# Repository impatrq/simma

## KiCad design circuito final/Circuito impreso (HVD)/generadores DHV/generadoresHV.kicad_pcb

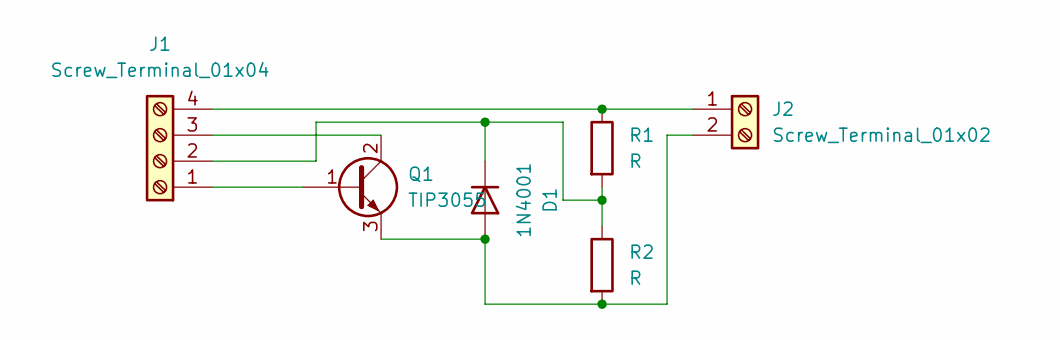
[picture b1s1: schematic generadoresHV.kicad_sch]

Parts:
D1: 1N4001; D_DO-41_SOD81_P10.16mm_Horizontal
J1: Screw_Terminal_01x04; TerminalBlock_bornier-4_P5.08mm
J2: Screw_Terminal_01x02; TerminalBlock_bornier-2_P5.08mm
Q1: TIP3055; TO-218-3_Vertical
R1, R2: R; R_Axial_Power_L20.0mm_W6.4mm_P7.62mm_Vertical

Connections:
unnamed: D1.1 (K), J1.2, R1.2, R2.1
unnamed: D1.2 (A), J2.2, Q1.3 (E), R2.2
unnamed: J1.1, Q1.1 (B)
unnamed: J1.3, Q1.2 (C)
unnamed: J1.4, J2.1, R1.1

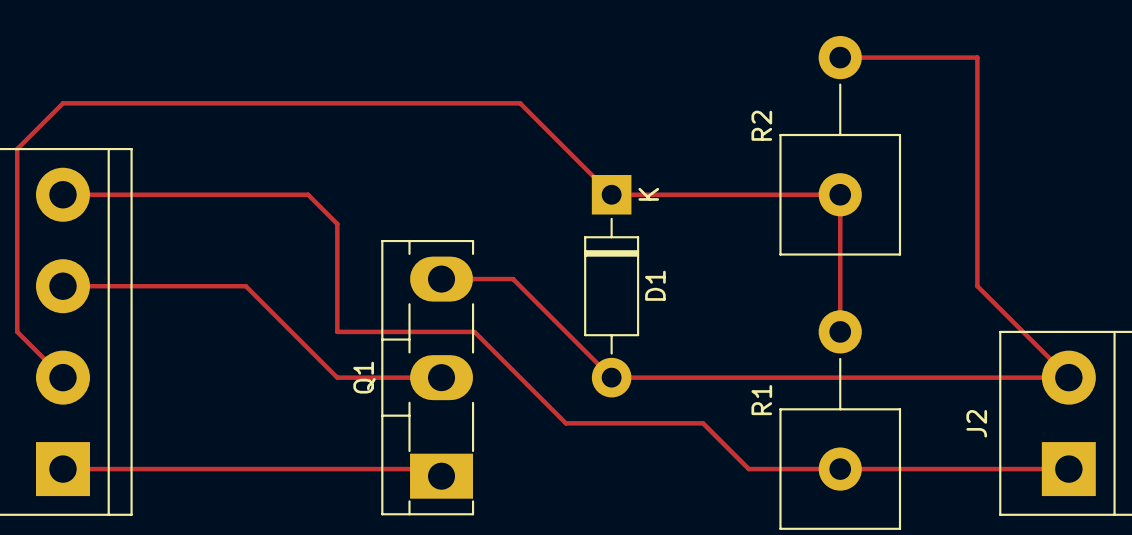
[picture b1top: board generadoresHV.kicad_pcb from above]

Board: 2 copper layers, 6 parts (0 on the bottom side), 5 nets.

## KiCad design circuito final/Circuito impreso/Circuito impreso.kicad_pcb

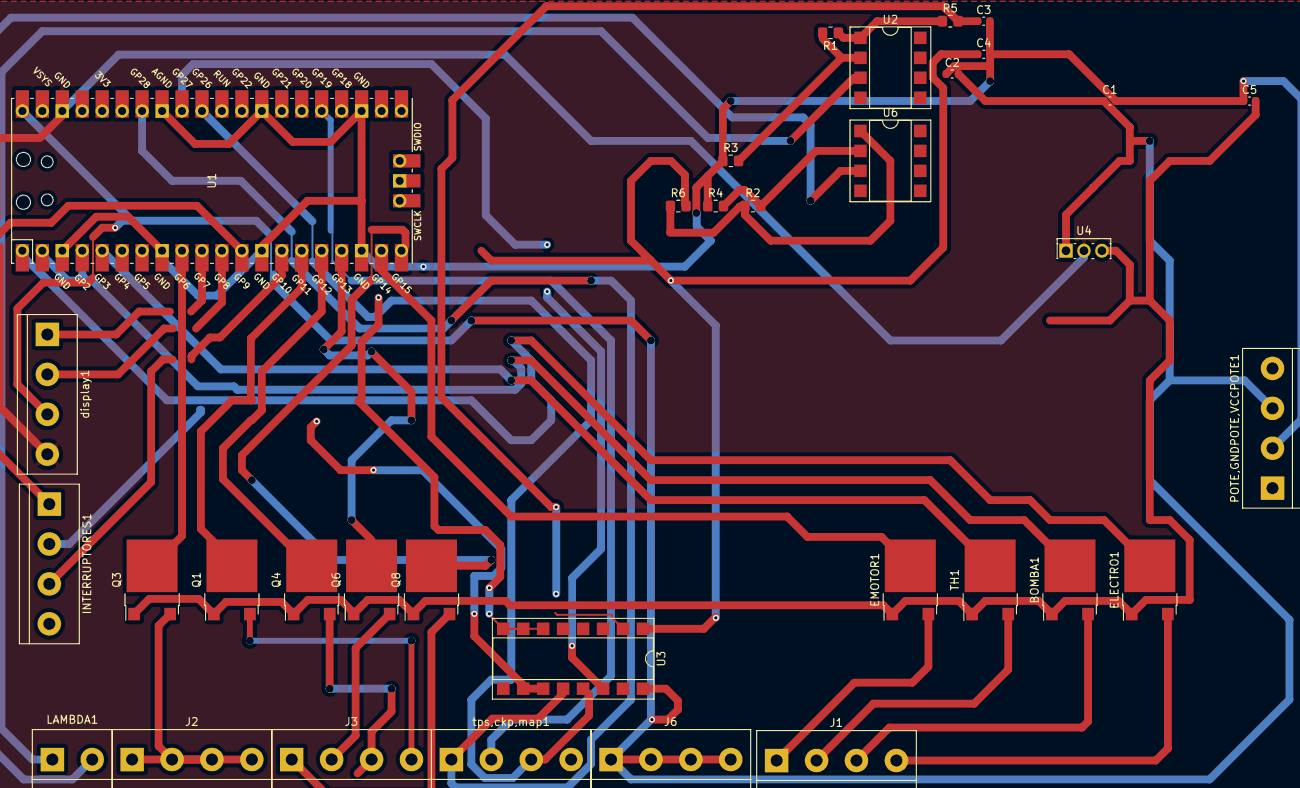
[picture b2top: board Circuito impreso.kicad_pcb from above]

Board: 2 copper layers, 34 parts (0 on the bottom side), 40 nets.

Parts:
BOMBA1: .; ATPAK-2
C1, C2, C3, C4, C5: C; C_0603_1608Metric
ELECTRO1: .; ATPAK-2
EMOTOR1: .; ATPAK-2
INTERRUPTORES1: .; TerminalBlock_bornier-4_P5.08mm
J1: ACTUADORES; TerminalBlock_bornier-4_P5.08mm
J2: INYECTORES; TerminalBlock_bornier-4_P5.08mm
J3: BANCADA 1; TerminalBlock_bornier-4_P5.08mm
J6: Vsensores; TerminalBlock_bornier-4_P5.08mm
LAMBDA1: TEMP; TerminalBlock_bornier-2_P5.08mm
POTE,GNDPOTE,VCCPOTE1: .; TerminalBlock_bornier-4_P5.08mm
Q1, Q3, Q4, Q6, Q8: .; ATPAK-2
R1, R2, R3, R4, R5, R6: R; R_0805_2012Metric_Pad1.20x1.40mm_HandSolder
TH1: .; ATPAK-2
U1: Pico; RPi_Pico_SMD_TH
U2, U6: LM358; DIP-8_W7.62mm_SMDSocket_SmallPads
U3: CD4053B; DIP-16_W7.62mm_SMDSocket_SmallPads
U4: L7805; SIPAK_Vertical
display1: .; TerminalBlock_bornier-4_P5.08mm
tps,ckp,map1: .; TerminalBlock_bornier-4_P5.08mm

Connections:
+12V: BOMBA1.1 (S), C5.2, ELECTRO1.1 (S), EMOTOR1.1 (S), Q1.1 (S), Q3.1 (S), Q4.1 (S), Q6.1 (S), Q8.1 (S), TH1.1 (S), U4.3 (OUT)
ADC1: U1.32 (GPIO27_ADC1), U3.14 (A)
Earth: C1.2, C2.1, C3.2, C4.2, C5.1, POTE,GNDPOTE,VCCPOTE1.2, R3.1, R4.1, U1.3 (GND), U1.8 (GND), U1.13 (GND), U1.18 (GND), U1.23 (GND), U1.28 (GND), U1.33 (AGND), U3.6 (INH), U3.7 (VEE), U3.8 (VSS)
GND: U1.38 (GND), U4.2 (GND), display1.4
GP00: ELECTRO1.2 (G), U1.1 (GPIO0)
GP02: BOMBA1.2 (G), INTERRUPTORES1.2, U1.2 (GPIO1), U1.4 (GPIO2)
GP03: TH1.2 (G), U1.5 (GPIO3)
GP06: Q3.2 (G), U1.9 (GPIO6)
GP07: U1.10 (GPIO7), display1.1
GP08: U1.11 (GPIO8), display1.2
GP09: INTERRUPTORES1.1, U1.12 (GPIO9)
GP010: INTERRUPTORES1.3, U1.14 (GPIO10)
GP014: EMOTOR1.2 (G), U1.19 (GPIO14)
GP019: U1.25 (GPIO19), tps,ckp,map1.2
unnamed: BOMBA1.3 (D), J1.3
unnamed: C3.1, R5.2, U3.2 (B0)
unnamed: C4.1, R6.2, U3.1 (B1)
unnamed: ELECTRO1.3 (D), J1.4
unnamed: EMOTOR1.3 (D), J1.1
unnamed: J1.2, TH1.3 (D)
unnamed: J2.1, J2.2, J2.3, J2.4, Q3.3 (D)
unnamed: J3.1, Q8.3 (D)
unnamed: J3.2, Q6.3 (D)
unnamed: J3.3, Q4.3 (D)
unnamed: J3.4, Q1.3 (D)
unnamed: LAMBDA1.1, U2.3 (+)
unnamed: LAMBDA1.2, U6.3 (+)
unnamed: Q1.2 (G), U1.15 (GPIO11)
unnamed: Q4.2 (G), U1.16 (GPIO12)
unnamed: Q6.2 (G), U1.17 (GPIO13)
unnamed: Q8.2 (G), U1.20 (GPIO15)
unnamed: R1.1, R5.1, U2.1
unnamed: R1.2, R3.2, U2.2 (-)
unnamed: R2.1, R6.1, U6.1
unnamed: R2.2, R4.2, U6.2 (-)
unnamed: U1.29 (GPIO22), U3.10 (S2), U3.11 (S1)
unnamed: U1.35 (ADC_VREF), U1.36 (3V3)
unnamed: U1.34 (GPIO28_ADC2), U3.12 (A0), tps,ckp,map1.1
unnamed: U1.31 (GPIO26_ADC0), U3.13 (A1), tps,ckp,map1.3
VBUS: C1.1, C2.2, J6.1, J6.2, J6.3, J6.4, POTE,GNDPOTE,VCCPOTE1.3, U1.40 (VBUS), U3.16 (VDD), U4.1 (IN), display1.3

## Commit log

2022-06-09 chore: agregar circuito
2022-06-09 docs: agregar datasheets
2022-06-09 chore: agregar circuito (#1)
    * chore: agregar circuito
    * docs: agregar datasheets
